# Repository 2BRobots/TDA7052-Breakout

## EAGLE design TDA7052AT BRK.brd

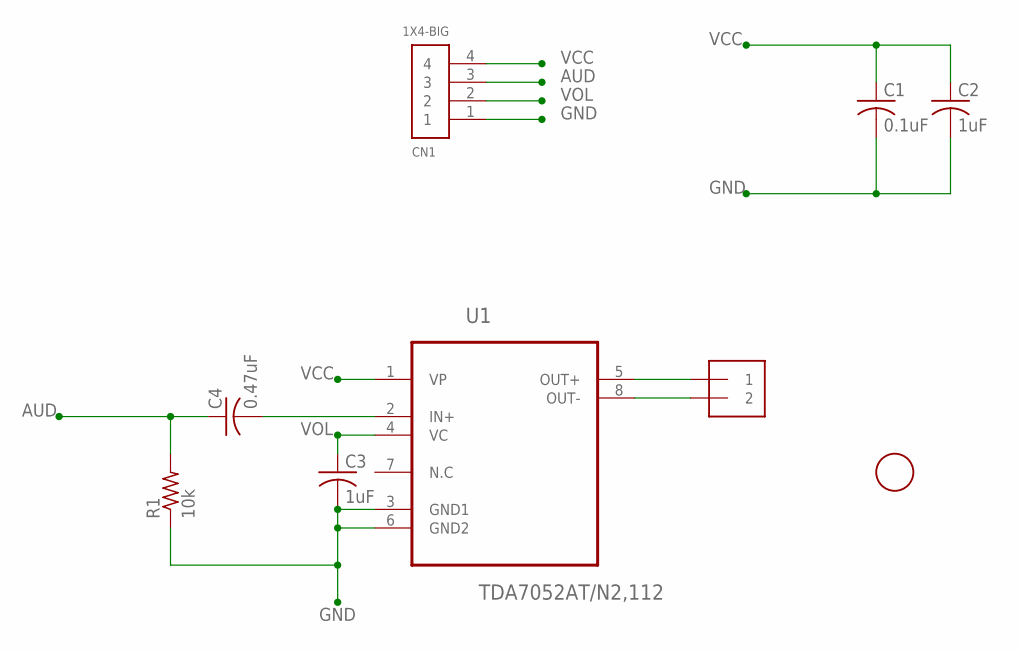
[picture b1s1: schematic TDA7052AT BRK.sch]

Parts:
C1: 0.1uF; C0603K
C2, C3: 1uF; C0603K
C4: 0.47uF; C0805K
CN1: 1X4-BIG; 1X04-BIG
J1: 1X2-3.5MM
R1: 10k; R0805
U1: TDA7052AT/N2,112; SOIC127P600X175-8N
U$1: FIDUCIAL; FIDUCIAL_1MM

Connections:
AUD: C4.1, CN1.3, R1.2
GND: C1.2, C2.2, C3.2, CN1.1, R1.1, U1.3 (GND1), U1.6 (GND2)
unnamed: J1.2, U1.8 (OUT-)
unnamed: J1.1, U1.5 (OUT+)
unnamed: C4.2, U1.2 (IN+)
VCC: C1.1, C2.1, CN1.4, U1.1 (VP)
VOL: C3.1, CN1.2, U1.4 (VC)

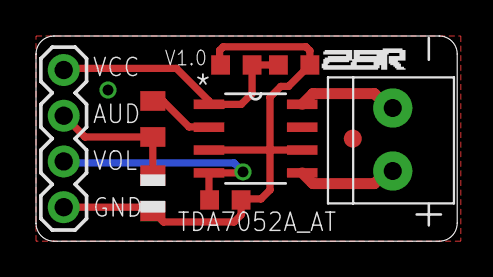
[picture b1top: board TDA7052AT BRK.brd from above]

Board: 2 copper layers, 23.4 x 11.4 mm, 9 parts (0 on the bottom side), 7 nets.

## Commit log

2018-09-06 added schematic in pdf
